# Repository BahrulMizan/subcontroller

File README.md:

# subcontroller
> skripsi subcontroller

## required
- [x] skematik controller(opencm)
- [x] board controller

## author
> Bahrul Mizan

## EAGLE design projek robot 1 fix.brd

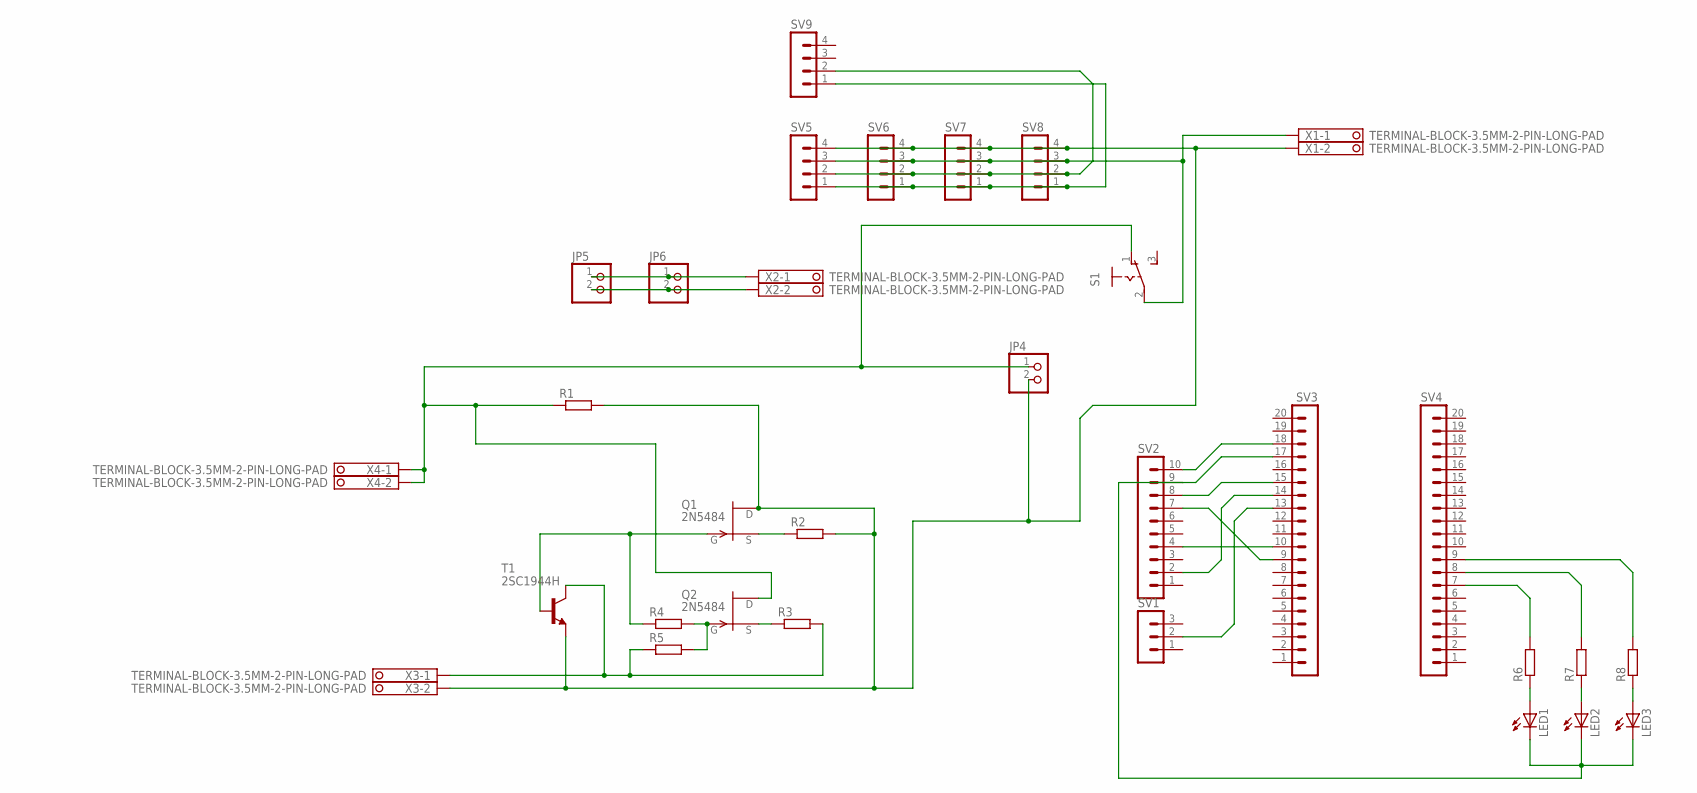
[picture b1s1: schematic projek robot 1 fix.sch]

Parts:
JP4, JP5, JP6: PINHD-1X2; 1X02
LED1, LED2, LED3: LED5MM
Q1, Q2: 2N5484; TO92-
R1, R2, R3, R4, R5, R6, R7, R8: R-EU_0207/7; 0207/7
S1: M251
SV1: MA03-1
SV2: MA10-1
SV3, SV4: MA20-1
SV5, SV6, SV7, SV8, SV9: MA04-1
T1: 2SC1944H; T-30
X1, X2, X3, X4: TERMINAL-BLOCK-3.5MM-2-PIN-LONG-PAD; TERMINAL-BLOCK-2-PIN-3.5MM-LONG-PAD

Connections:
unnamed: Q2.2 (S), R3.1
unnamed: Q1.2 (S), R2.1
unnamed: Q2.1 (G), R4.2, R5.2
unnamed: Q1.1 (G), R4.1, T1.1 (B)
unnamed: JP5.1, JP6.1, X2.1
unnamed: R3.2, R5.1, T1.2 (C), X3.1
unnamed: JP4.1, Q2.3 (D), R1.1, S1.1 (O), X4.1, X4.2
unnamed: SV2.10, SV3.18
unnamed: SV2.8, SV3.15
unnamed: SV2.7, SV3.9
unnamed: SV2.2, SV3.14
unnamed: SV2.4, SV3.10
unnamed: SV1.2, SV3.13
unnamed: LED1.A, R6.1
unnamed: LED2.A, R7.1
unnamed: LED3.A, R8.1
unnamed: R6.2, SV4.7
unnamed: R7.2, SV4.8
unnamed: R8.2, SV4.9
unnamed: JP4.2, Q1.3 (D), R1.2, R2.2, SV5.4, SV6.4, SV7.4, SV8.4, T1.3 (E), X1.2, X3.2
unnamed: S1.2, SV5.3, SV6.3, SV7.3, SV8.3, X1.1
unnamed: SV5.2, SV6.2, SV7.2, SV8.2, SV9.2
unnamed: JP5.2, JP6.2, X2.2
unnamed: SV5.1, SV6.1, SV7.1, SV8.1, SV9.1
unnamed: LED1.K (C), LED2.K (C), LED3.K (C), SV2.9, SV3.17

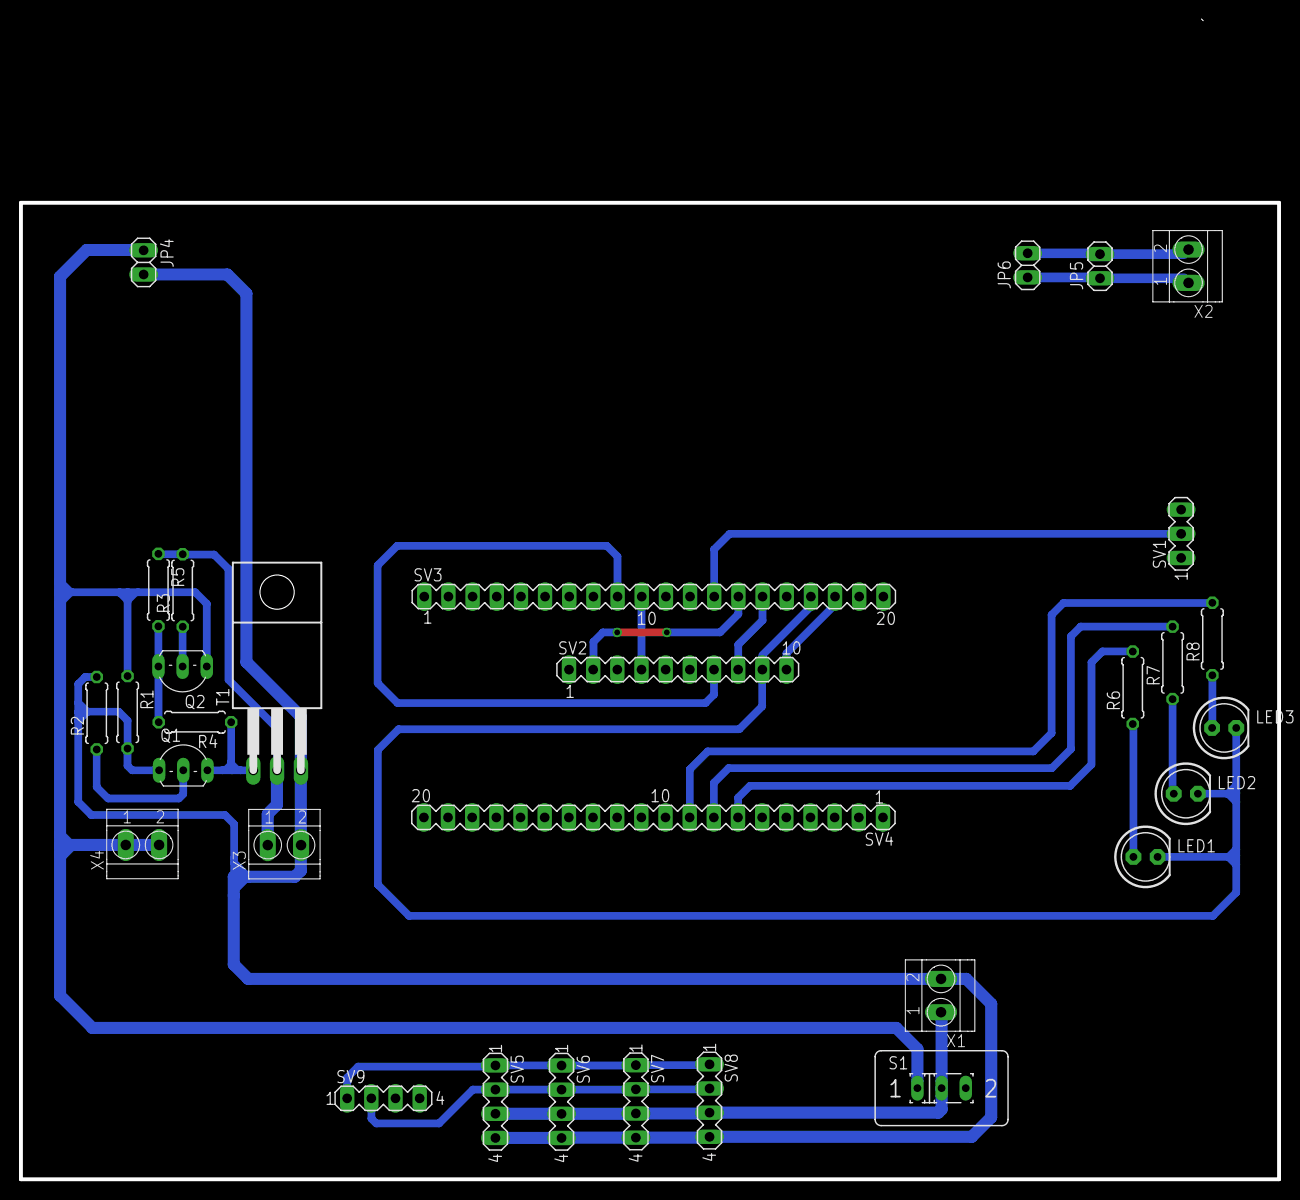
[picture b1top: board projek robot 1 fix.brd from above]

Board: 2 copper layers, 132.2 x 121.8 mm, 31 parts (0 on the bottom side), 25 nets.
